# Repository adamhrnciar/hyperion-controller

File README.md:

# Hyperion: antweight combat robot controller

Open-source all-in-one controller for 150 g antweight combat robots. It combines an RC receiver
input, two brushed drive motor drivers, power handling and an IMU on a 34 × 28 mm 2-layer board.

Designed by Team Hyperion (Faculty of Electrical Engineering and Communication, Brno University of
Technology) for the Czech Combat Robot League (Česká liga bojových robotů, FLS Battlebots).

| Top | Bottom |
|---|---|
|  |  |

## Status

**Revision v1.2: unbuilt prototype; ordering is on hold.** The recovered 2026-11-13 Konnect review
reported no DRC, connectivity or schematic-parity violations and one understood ERC warning on
the IMU's unused SDx pin. Assembly process, sourcing and the remaining checks in the
[pre-order review](docs/v1.2-preorder-review-2026-11-13.md) still need resolution. Prototype build
and physical bring-up have not happened.

## Features

- **MCU:** RP2354A (RP2350 with 2 MB internal flash), 12 MHz crystal
- **Drive:** 2× TI DRV8231A brushed H-bridge, 4.5–33 V, current limit about 1.5 A per channel
  (IPROPI current regulation). Current feedback goes to the ADC for telemetry.
- **Input power:** 2–4S LiPo
  - reverse-polarity protection (AON7403 P-FET)
  - SMF18A TVS
  - battery voltage sensing
- **Rails:**
  - 5 V buck (LMR51610) for the receiver and servo/ESC signal header
  - 3.3 V LDO (ME6211)
- **Receiver input:** universal UART/RC pads for ELRS/CRSF, SBUS, iBUS and PPM, with a 5 V supply
  for the receiver
- **Outputs:** 4 PWM pads (weapon ESC, servo, spare), each with a 5 V/GND pad
- **IMU:** LSM6DSV32X (±32 g) for auto-invert and heading hold
- **Programming:** USB pads (UF2 bootloader, BOOT pad) and SWD pads
- **Status LEDs:** red and green
- **Board:** 34 × 28 mm, 2 layers, 1.6 mm FR-4. Battery and motor pads sit on the board edge.

## Motor target

- **Drive target:** 1–2 N10/N20 gearmotors per side on a 2–4S supply, with about 1.5 A regulated
  per channel (1.47 A nominal, set by R_IPROPI = 1.5 kΩ with VREF on 3.3 V). Motors sharing a
  channel share that limit. Choose motors rated for the applied voltage; this is not a claim
  that every N10/N20 is suitable for direct 4S operation.
- **Thermal limit:** 1.47 A is a current-regulation setting, not a measured continuous rating.
  Sustained pushing and stall tests on 2S, 3S and 4S remain open. Do not increase the limit to
  compensate for a motor that stalls above it.
- **Compared with the Malenki Nano HV** (1 A continuous / 3 A peak on 3 channels, AFHDS 2A
  receiver only, no BEC): Hyperion targets the same small-motor class and adds a 5 V BEC, an IMU,
  current/battery sensing and external receiver inputs. Its continuous rating still needs
  measurement, and its nominal regulated limit is 1.47 A rather than a specified 3 A burst.
  Firmware currently supports SBUS, CRSF and two-channel PWM; transmitter telemetry, iBUS and
  PPM are planned.
- **Not for beetleweight drive.** Beetleweight drive motors need 5–12 A per channel. Hyperion can
  still be the brain of such a robot, driving external ESCs from its PWM pads.

## Repository layout

```
hardware/   KiCad 10 project (schematic, PCB, project symbol and footprint libraries)
fab/        Manufacturing files for v1.2: Gerbers + drill (zip), BOM, pick-and-place, DRC report
docs/       Schematic PDF
firmware/   Firmware (Raspberry Pi Pico SDK, C) and the bring-up plan
images/     Renders and logo
```

## Building

- **PCB:** upload `fab/hyperion-v1.2-gerbers.zip`. 2 layers, 1.6 mm. Smallest features: 0.2 mm
  track/space and 0.3 mm drill. The RP2354A's 0.4 mm-pitch QFN needs a stencil.
- **Assembly:** `fab/hyperion-v1.2-bom.csv` lists LCSC and manufacturer part numbers.
  `fab/hyperion-v1.2-pos.csv` has the pick-and-place data. C3, the 100 µF bulk capacitor, is not
  placed; it is hand-wired to its pads. The TPx test pads are bare pads with no part.
- **PCBWay:** `fab/pcbway/` holds the candidate package: Gerbers, a BOM and centroid file with only
  the assembled parts, and `ASSEMBLY_NOTES.md` (board specs, DNP list, polarity notes, sourcing).
  Resolve the [pre-order review](docs/v1.2-preorder-review-2026-11-13.md) before releasing it.
- **Opening the design:** requires KiCad 10. The custom symbols and footprints are in
  `hardware/hyperion.kicad_sym` and `hardware/hyperion.pretty`.
- **Source of truth:** develop in [hyperion-controller](https://github.com/adamhrnciar/hyperion-controller).
  The `hyperion-controller/` subtree in `antweight-analysis` is a mirror. Its older
  `antweight/pcb/hyperion/` directory is historical; do not generate new manufacturing files from it.

## Firmware

`firmware/` holds the first firmware, written in C with the Raspberry Pi Pico SDK. It builds, but
has not run on a board yet. [firmware/README.md](firmware/README.md) covers building, settings,
stick and motor conventions, and the safety behaviour. [firmware/BRINGUP.md](firmware/BRINGUP.md)
is the test plan for the first boards.

Done:
- SBUS, CRSF and PWM receiver input with failsafe. On signal loss the drive motors brake and the
  weapon ESC gets no pulses.
- Arming interlock: the robot only arms with the drive stick centred and the weapon stick down.
  A dropout shorter than 1 s during a match resumes driving at once.
- tank mixing, DRV8231A drive, weapon ESC output on PWM1
- IMU, battery voltage and motor current readout
- bring-up test modes, including a stall test for the drivers' thermal shutdown

Planned:
- iBUS and PPM input
- IMU auto-invert and heading hold
- current and battery telemetry to the transmitter

## Buying a board

Assembled and tested boards will be sold once v1.2 has passed testing. Buying one supports
further development. You are also free to build your own from the files here.

## License

The hardware is licensed under [CERN-OHL-S-2.0](LICENSE). You may make, modify and sell the board,
as long as you publish the source of any modified version under the same licence.

The firmware in `firmware/` is licensed under [GPL-3.0-or-later](firmware/LICENSE). You may use,
modify and sell it, as long as you publish the source of any modified version you distribute under
the same licence. `firmware/pico_sdk_import.cmake` is BSD-3-Clause (Raspberry Pi Ltd).

The licence does not cover the name "Hyperion" or the Hyperion logo. Modified or third-party boards
must not be sold under that name or with that logo.

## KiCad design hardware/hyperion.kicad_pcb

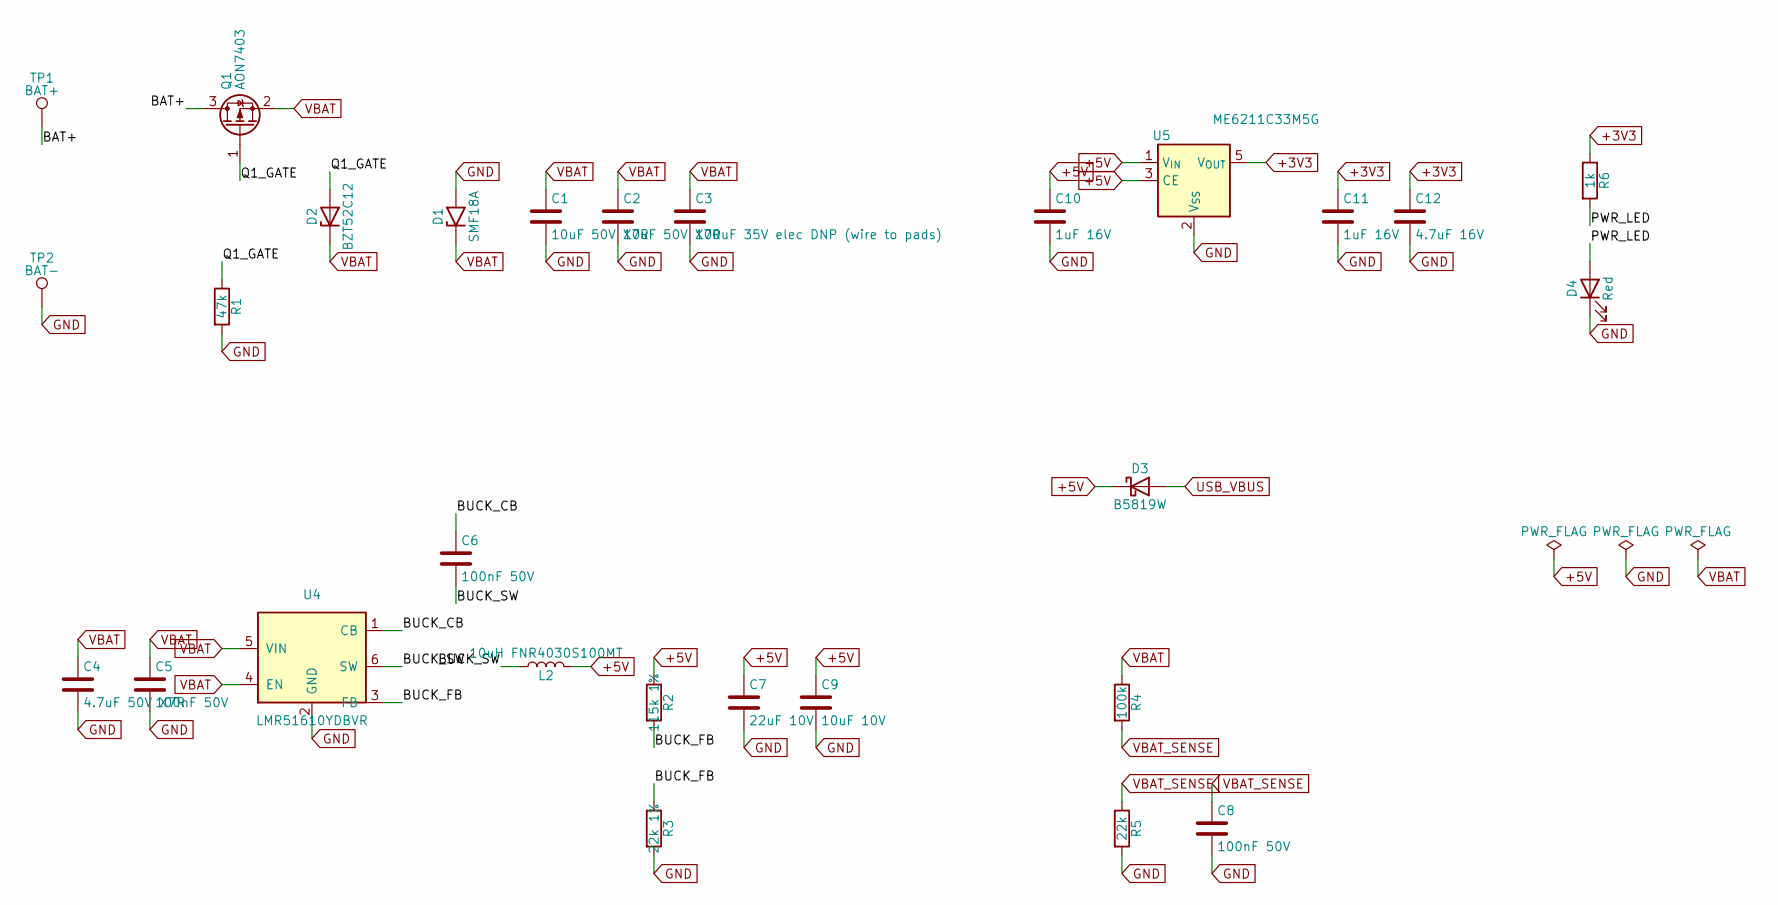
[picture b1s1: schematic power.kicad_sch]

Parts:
C1, C2: 10uF 50V X7R; C_1206_3216Metric; MPN CL31B106KBHNNNE; LCSC C89632
C3: 100uF 35V elec DNP (wire to pads); C_1206_3216Metric; MPN RVE100UF35V67RV0072 (optional, hand-wir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; LCSC C2836437
C4: 4.7uF 50V X7R; C_1206_3216Metric; MPN HGC1206R7475K500NSPJ; LCSC C7472974
C5, C6, C8: 100nF 50V; C_0603_1608Metric; MPN 0603B104M500NT; LCSC C286510
C7: 22uF 10V; C_0805_2012Metric; MPN CL21A226MPQNNNE; LCSC C29277
C9: 10uF 10V; C_0603_1608Metric; MPN CL10A106KP8NNNC; LCSC C19702
C10, C11: 1uF 16V; C_0603_1608Metric; MPN TCC0603X5R105K160CT; LCSC C696901
C12: 4.7uF 16V; C_0603_1608Metric; MPN CL10A475KO8NNNC; LCSC C19666
D1: SMF18A; D_SOD-123F; MPN SMF18A (JSCJ); LCSC C1509591
D2: BZT52C12; D_SOD-123; MPN BZT52C12 (MDD); LCSC C173429
D3: B5819W; D_SOD-123; MPN B5819W (MDD); LCSC C64885
D4: Red; LED_0603_1608Metric; MPN KT-0603R; LCSC C2286
L2: 10uH FNR4030S100MT; L_Changjiang_FNR4030S; MPN FNR4030S100MT; LCSC C167879
Q1: AON7403; AON7403_PowerPAK1212-8_GSD; MPN AON7403 (TECH PUBLIC); LCSC C5310961
R1: 47k; R_0603_1608Metric; MPN 0603WAF4702T5E; LCSC C25819
R2: 115k 1%; R_0603_1608Metric; MPN 0603WAF1153T5E; LCSC C22783
R3: 22k 1%; R_0603_1608Metric; MPN 0603WAF2202T5E; LCSC C31850
R4: 100k; R_0603_1608Metric; MPN 0603WAF1003T5E; LCSC C25803
R5: 22k; R_0603_1608Metric; MPN 0603WAF2202T5E; LCSC C31850
R6: 1k; R_0603_1608Metric; MPN 0603WAF1001T5E; LCSC C21190
TP1: BAT+; TestPoint_Pad_2.5x2.5mm
TP2: BAT-; TestPoint_Pad_2.5x2.5mm
U4: LMR51610YDBVR; SOT-23-6; MPN LMR51610YDBVR; LCSC C22427220
U5: ME6211C33M5G; SOT-23-5; MPN ME6211C33M5G-N; LCSC C82942

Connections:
+3V3: C11.1, C12.1, R6.1, U5.5 (V_{OUT}); also elsewhere on the board
+5V: C7.1, C9.1, C10.1, D3.1 (K), L2.2, R2.1, U5.1 (V_{IN}), U5.3 (CE); also elsewhere on the board
/Power/BAT+: Q1.3 (D), TP1.1 (1_1)
/Power/BUCK_CB: C6.1, U4.1 (CB)
/Power/BUCK_FB: R2.2, R3.1, U4.3 (FB)
/Power/BUCK_SW: C6.2, L2.1, U4.6 (SW)
/Power/PWR_LED: D4.2 (A), R6.2
/Power/Q1_GATE: D2.2 (A), Q1.1 (G), R1.1
GND: C1.2, C2.2, C3.2, C4.2, C5.2, C7.2, C8.2, C9.2, C10.2, C11.2, C12.2, D1.2 (A2), D4.1 (K), R1.2, R3.2, R5.2, TP2.1 (1_1), U4.2 (GND), U5.2 (V_{SS}); also elsewhere on the board
USB_VBUS: D3.2 (A); also elsewhere on the board
VBAT: C1.1, C2.1, C3.1, C4.1, C5.1, D1.1 (A1), D2.1 (K), Q1.2 (S), R4.1, U4.4 (EN), U4.5 (VIN); also elsewhere on the board
VBAT_SENSE: C8.1, R4.2, R5.1; also elsewhere on the board

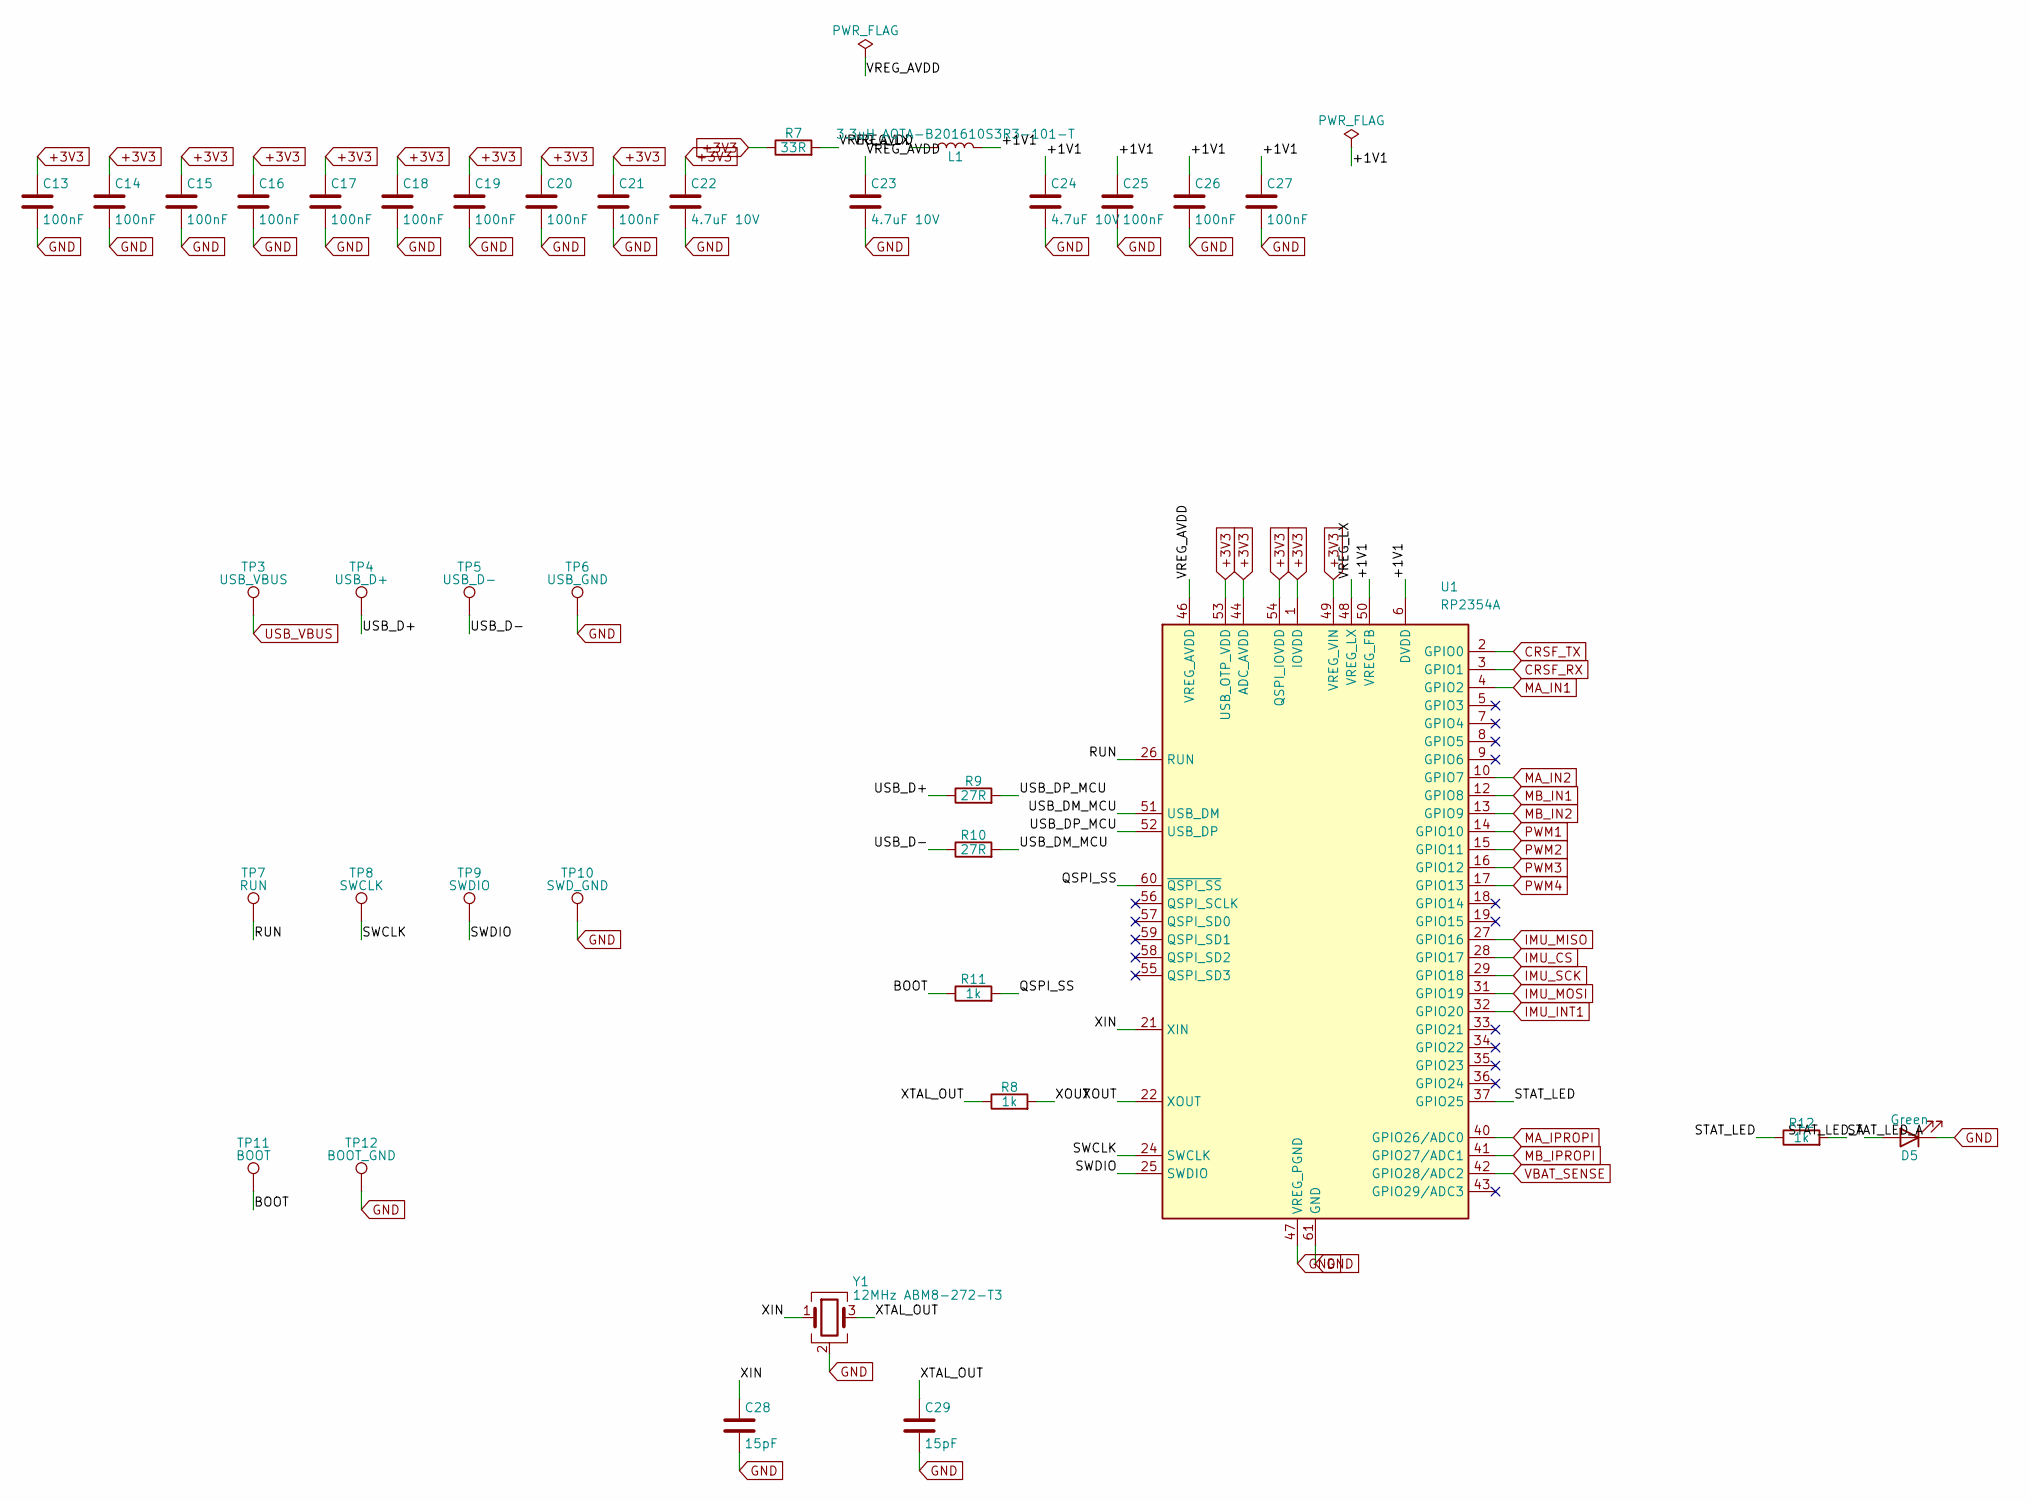
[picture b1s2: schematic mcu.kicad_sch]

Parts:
C13, C14, C15, C16, C17, C18, C19, C20, C21, C25, C26, C27: 100nF; C_0402_1005Metric; MPN CL05B104KO5NNNC; LCSC C1525
C22, C23, C24: 4.7uF 10V; C_0402_1005Metric; MPN CL05A475MP5NRNC; LCSC C23733
C28, C29: 15pF; C_0402_1005Metric; MPN 0402CG150J500NT; LCSC C1548
D5: Green; LED_0603_1608Metric; MPN P2-0603G1TS2-06T-002; LCSC C7496818
L1: 3.3uH AOTA-B201610S3R3-101-T; L_Murata_DFE201610P; MPN AOTA-B201610S3R3-101-T; LCSC C42411119
R7: 33R; R_0402_1005Metric; MPN 0402WGF330JTCE; LCSC C25105
R8, R11, R12: 1k; R_0402_1005Metric; MPN 0402WGF1001TCE; LCSC C11702
R9, R10: 27R; R_0402_1005Metric; MPN RC-02K27R0FT; LCSC C140174
TP3: USB_VBUS; TestPoint_Pad_1.0x1.0mm
TP4: USB_D+; TestPoint_Pad_1.0x1.0mm
TP5: USB_D-; TestPoint_Pad_1.0x1.0mm
TP6: USB_GND; TestPoint_Pad_1.0x1.0mm
TP7: RUN; TestPoint_Pad_1.0x1.0mm
TP8: SWCLK; TestPoint_Pad_1.0x1.0mm
TP9: SWDIO; TestPoint_Pad_1.0x1.0mm
TP10: SWD_GND; TestPoint_Pad_1.0x1.0mm
TP11: BOOT; TestPoint_Pad_1.0x1.0mm
TP12: BOOT_GND; TestPoint_Pad_1.0x1.0mm
U1: RP2354A; RP2354A_QFN-60_CircuitNinja; MPN RP2354A; LCSC C41378174
Y1: 12MHz ABM8-272-T3; Crystal_SMD_3225-4Pin_3.2x2.5mm; MPN ABM8-272-T3; LCSC C20625731

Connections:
+3V3: C13.1, C14.1, C15.1, C16.1, C17.1, C18.1, C19.1, C20.1, C21.1, C22.1, R7.1, U1.1 (IOVDD), U1.11 (IOVDD), U1.20 (IOVDD), U1.30 (IOVDD), U1.38 (IOVDD), U1.44 (ADC_AVDD), U1.45 (IOVDD), U1.49 (VREG_VIN), U1.53 (USB_OTP_VDD), U1.54 (QSPI_IOVDD); also elsewhere on the board
/MCU/+1V1: C24.1, C25.1, C26.1, C27.1, L1.2, U1.6 (DVDD), U1.23 (DVDD), U1.39 (DVDD), U1.50 (VREG_FB)
/MCU/BOOT: R11.1, TP11.1 (1_1)
/MCU/QSPI_SS: R11.2, U1.60 (~QSPI_SS)
/MCU/RUN: TP7.1 (1_1), U1.26 (RUN)
/MCU/STAT_LED: R12.1, U1.37 (GPIO25)
/MCU/STAT_LED_A: D5.2 (A), R12.2
/MCU/SWCLK: TP8.1 (1_1), U1.24 (SWCLK)
/MCU/SWDIO: TP9.1 (1_1), U1.25 (SWDIO)
/MCU/USB_D+: R9.1, TP4.1 (1_1)
/MCU/USB_D-: R10.1, TP5.1 (1_1)
/MCU/USB_DM_MCU: R10.2, U1.51 (USB_DM)
/MCU/USB_DP_MCU: R9.2, U1.52 (USB_DP)
/MCU/VREG_AVDD: C23.1, R7.2, U1.46 (VREG_AVDD)
/MCU/VREG_LX: L1.1, U1.48 (VREG_LX)
/MCU/XIN: C28.1, U1.21 (XIN), Y1.1
/MCU/XOUT: R8.2, U1.22 (XOUT)
/MCU/XTAL_OUT: C29.1, R8.1, Y1.3
CRSF_RX: U1.3 (GPIO1); also elsewhere on the board
CRSF_TX: U1.2 (GPIO0); also elsewhere on the board
GND: C13.2, C14.2, C15.2, C16.2, C17.2, C18.2, C19.2, C20.2, C21.2, C22.2, C23.2, C24.2, C25.2, C26.2, C27.2, C28.2, C29.2, D5.1 (K), TP6.1 (1_1), TP10.1 (1_1), TP12.1 (1_1), U1.47 (VREG_PGND), U1.61 (GND), Y1.2 (G), Y1.4 (G); also elsewhere on the board
IMU_CS: U1.28 (GPIO17); also elsewhere on the board
IMU_INT1: U1.32 (GPIO20); also elsewhere on the board
IMU_MISO: U1.27 (GPIO16); also elsewhere on the board
IMU_MOSI: U1.31 (GPIO19); also elsewhere on the board
IMU_SCK: U1.29 (GPIO18); also elsewhere on the board
MA_IN1: U1.4 (GPIO2); also elsewhere on the board
MA_IN2: U1.10 (GPIO7); also elsewhere on the board
MA_IPROPI: U1.40 (GPIO26/ADC0); also elsewhere on the board
MB_IN1: U1.12 (GPIO8); also elsewhere on the board
MB_IN2: U1.13 (GPIO9); also elsewhere on the board
MB_IPROPI: U1.41 (GPIO27/ADC1); also elsewhere on the board
PWM1: U1.14 (GPIO10); also elsewhere on the board
PWM2: U1.15 (GPIO11); also elsewhere on the board
PWM3: U1.16 (GPIO12); also elsewhere on the board
PWM4: U1.17 (GPIO13); also elsewhere on the board
USB_VBUS: TP3.1 (1_1); also elsewhere on the board
VBAT_SENSE: U1.42 (GPIO28/ADC2); also elsewhere on the board

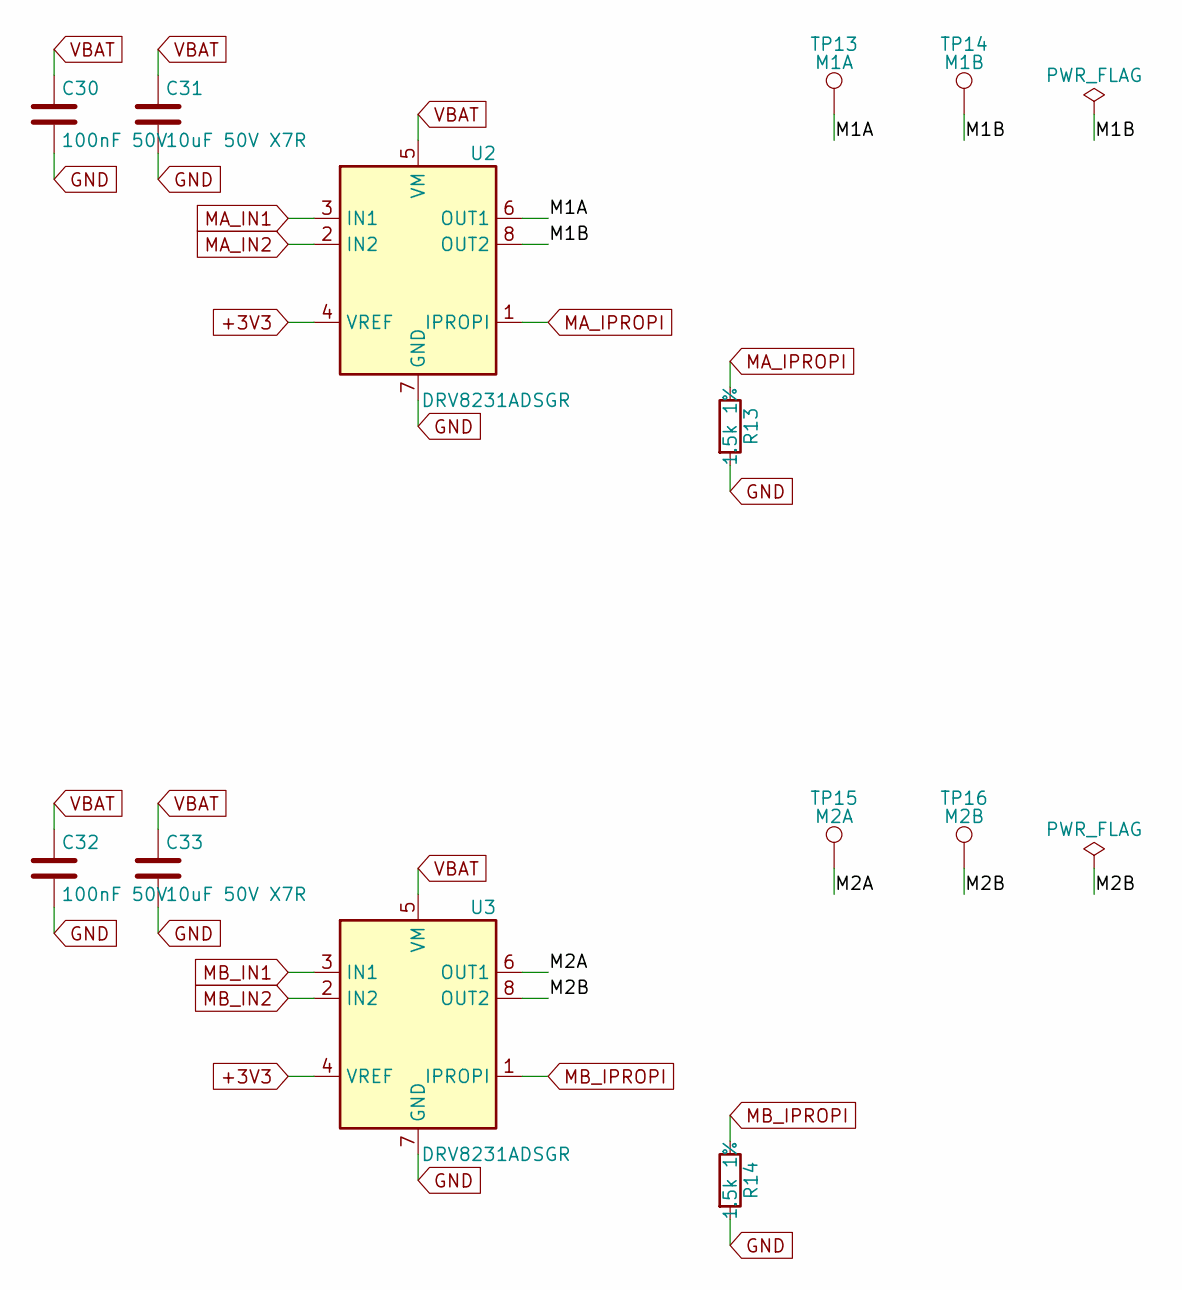
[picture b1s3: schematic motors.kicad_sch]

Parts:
C30, C32: 100nF 50V; C_0603_1608Metric; MPN 0603B104M500NT; LCSC C286510
C31, C33: 10uF 50V X7R; C_1206_3216Metric; MPN CL31B106KBHNNNE; LCSC C89632
R13, R14: 1.5k 1%; R_0603_1608Metric; MPN 0603WAF1501T5E; LCSC C22843
TP13: M1A; TestPoint_Pad_2.0x2.0mm
TP14: M1B; TestPoint_Pad_2.0x2.0mm
TP15: M2A; TestPoint_Pad_2.0x2.0mm
TP16: M2B; TestPoint_Pad_2.0x2.0mm
U2, U3: DRV8231ADSGR; Texas_DSG0008A_WSON-8-1EP_2x2mm_P0.5mm_EP0.9x1.6mm; MPN DRV8231ADSGR; LCSC C5139865

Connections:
+3V3: U2.4 (VREF), U3.4 (VREF); also elsewhere on the board
/Motors/M1A: TP13.1 (1_1), U2.6 (OUT1)
/Motors/M1B: TP14.1 (1_1), U2.8 (OUT2)
/Motors/M2A: TP15.1 (1_1), U3.6 (OUT1)
/Motors/M2B: TP16.1 (1_1), U3.8 (OUT2)
GND: C30.2, C31.2, C32.2, C33.2, R13.2, R14.2, U2.7 (GND), U2.9 (GND), U3.7 (GND), U3.9 (GND); also elsewhere on the board
MA_IN1: U2.3 (IN1); also elsewhere on the board
MA_IN2: U2.2 (IN2); also elsewhere on the board
MA_IPROPI: R13.1, U2.1 (IPROPI); also elsewhere on the board
MB_IN1: U3.3 (IN1); also elsewhere on the board
MB_IN2: U3.2 (IN2); also elsewhere on the board
MB_IPROPI: R14.1, U3.1 (IPROPI); also elsewhere on the board
VBAT: C30.1, C31.1, C32.1, C33.1, U2.5 (VM), U3.5 (VM); also elsewhere on the board

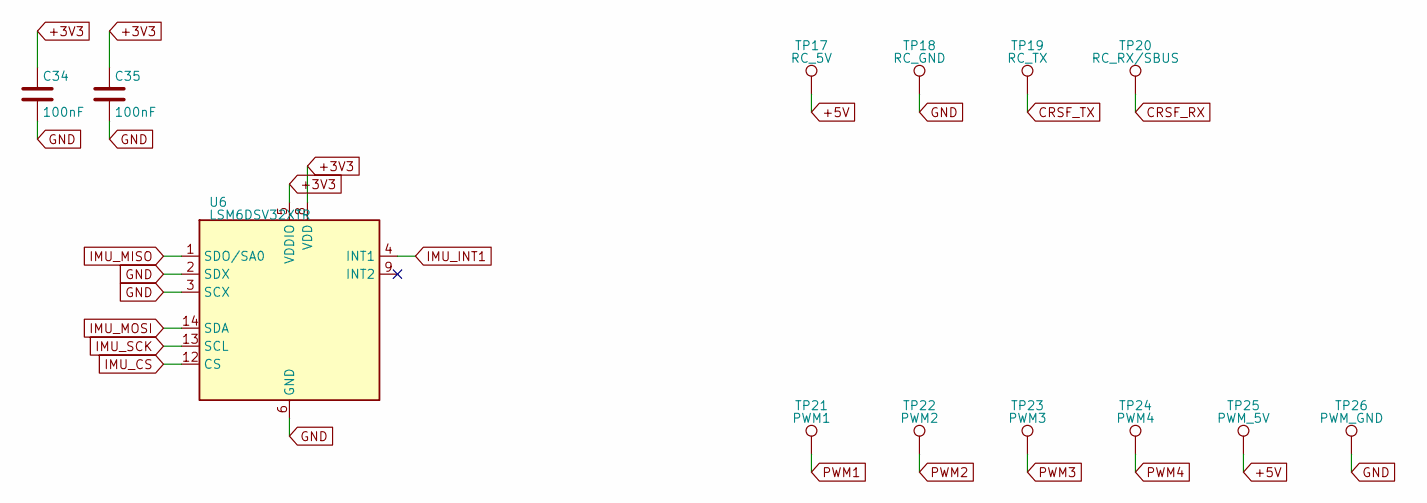
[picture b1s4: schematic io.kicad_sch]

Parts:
C34, C35: 100nF; C_0402_1005Metric; MPN CL05B104KO5NNNC; LCSC C1525
TP17: RC_5V; TestPoint_Pad_1.0x1.0mm
TP18: RC_GND; TestPoint_Pad_1.0x1.0mm
TP19: RC_TX; TestPoint_Pad_1.0x1.0mm
TP20: RC_RX/SBUS; TestPoint_Pad_1.0x1.0mm
TP21: PWM1; TestPoint_Pad_1.0x1.0mm
TP22: PWM2; TestPoint_Pad_1.0x1.0mm
TP23: PWM3; TestPoint_Pad_1.0x1.0mm
TP24: PWM4; TestPoint_Pad_1.0x1.0mm
TP25: PWM_5V; TestPoint_Pad_1.0x1.0mm
TP26: PWM_GND; TestPoint_Pad_1.0x1.0mm
U6: LSM6DSV32XTR; LGA-14_3x2.5mm_P0.5mm_CircuitNinja; MPN LSM6DSV32XTR; LCSC C22461202

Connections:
+3V3: C34.1, C35.1, U6.5 (VDDIO), U6.8 (VDD); also elsewhere on the board
+5V: TP17.1 (1_1), TP25.1 (1_1); also elsewhere on the board
CRSF_RX: TP20.1 (1_1); also elsewhere on the board
CRSF_TX: TP19.1 (1_1); also elsewhere on the board
GND: C34.2, C35.2, TP18.1 (1_1), TP26.1 (1_1), U6.2 (SDX), U6.3 (SCX), U6.6 (GND), U6.7 (GND); also elsewhere on the board
IMU_CS: U6.12 (CS); also elsewhere on the board
IMU_INT1: U6.4 (INT1); also elsewhere on the board
IMU_MISO: U6.1 (SDO/SA0); also elsewhere on the board
IMU_MOSI: U6.14 (SDA); also elsewhere on the board
IMU_SCK: U6.13 (SCL); also elsewhere on the board
PWM1: TP21.1 (1_1); also elsewhere on the board
PWM2: TP22.1 (1_1); also elsewhere on the board
PWM3: TP23.1 (1_1); also elsewhere on the board
PWM4: TP24.1 (1_1); also elsewhere on the board

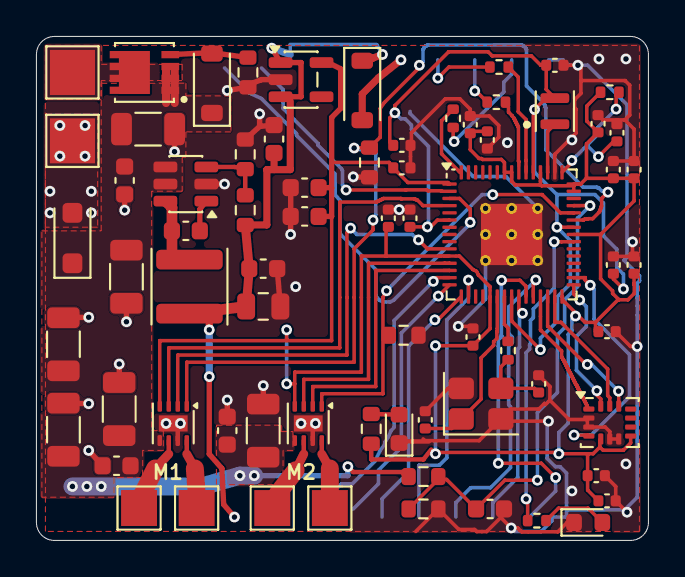
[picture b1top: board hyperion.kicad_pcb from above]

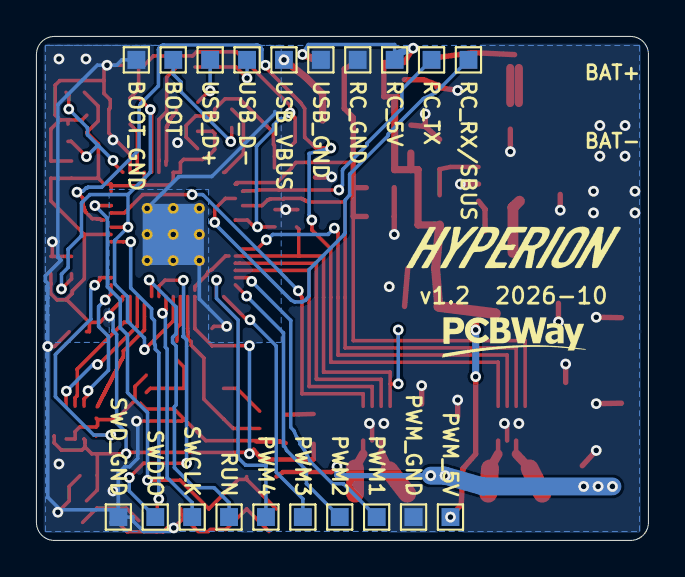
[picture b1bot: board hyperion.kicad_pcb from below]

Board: 2 copper layers, 34.0 x 28.0 mm, 90 parts (20 on the bottom side), 50 nets.

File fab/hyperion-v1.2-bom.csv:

"Reference","Value","Footprint","QUANTITY","DNP","LCSC","MPN"
"C1,C2,C31,C33","10uF 50V X7R","Capacitor_SMD:C_1206_3216Metric","4","","C89632","CL31B106KBHNNNE"
"C3","100uF 35V elec DNP (wire to pads)","Capacitor_SMD:C_1206_3216Metric","1","","C2836437","RVE100UF35V67RV0072 (optional, hand-wired)"
"C4","4.7uF 50V X7R","Capacitor_SMD:C_1206_3216Metric","1","","C7472974","HGC1206R7475K500NSPJ"
"C5,C6,C8,C30,C32","100nF 50V","Capacitor_SMD:C_0603_1608Metric","5","","C286510","0603B104M500NT"
"C7","22uF 10V","Capacitor_SMD:C_0805_2012Metric","1","","C29277","CL21A226MPQNNNE"
"C9","10uF 10V","Capacitor_SMD:C_0603_1608Metric","1","","C19702","CL10A106KP8NNNC"
"C10,C11","1uF 16V","Capacitor_SMD:C_0603_1608Metric","2","","C696901","TCC0603X5R105K160CT"
"C12","4.7uF 16V","Capacitor_SMD:C_0603_1608Metric","1","","C19666","CL10A475KO8NNNC"
"C13-C21,C25-C27,C34,C35","100nF","Capacitor_SMD:C_0402_1005Metric","14","","C1525","CL05B104KO5NNNC"
"C22-C24","4.7uF 10V","Capacitor_SMD:C_0402_1005Metric","3","","C23733","CL05A475MP5NRNC"
"C28,C29","15pF","Capacitor_SMD:C_0402_1005Metric","2","","C1548","0402CG150J500NT"
"D1","SMF18A","Diode_SMD:D_SOD-123F","1","","C1509591","SMF18A (JSCJ)"
"D2","BZT52C12","Diode_SMD:D_SOD-123","1","","C173429","BZT52C12 (MDD)"
"D3","B5819W","Diode_SMD:D_SOD-123","1","","C64885","B5819W (MDD)"
"D4","Red","LED_SMD:LED_0603_1608Metric","1","","C2286","KT-0603R"
"D5","Green","LED_SMD:LED_0603_1608Metric","1","","C7496818","P2-0603G1TS2-06T-002"
"L1","3.3uH AOTA-B201610S3R3-101-T","Inductor_SMD:L_Murata_DFE201610P","1","","C42411119","AOTA-B201610S3R3-101-T"
"L2","10uH FNR4030S100MT","Inductor_SMD:L_Changjiang_FNR4030S","1","","C167879","FNR4030S100MT"
"Q1","AON7403","hyperion:AON7403_PowerPAK1212-8_GSD","1","","C5310961","AON7403 (TECH PUBLIC)"
"R1","47k","Resistor_SMD:R_0603_1608Metric","1","","C25819","0603WAF4702T5E"
"R2","115k 1%","Resistor_SMD:R_0603_1608Metric","1","","C22783","0603WAF1153T5E"
"R3","22k 1%","Resistor_SMD:R_0603_1608Metric","1","","C31850","0603WAF2202T5E"
"R4","100k","Resistor_SMD:R_0603_1608Metric","1","","C25803","0603WAF1003T5E"
"R5","22k","Resistor_SMD:R_0603_1608Metric","1","","C31850","0603WAF2202T5E"
"R6","1k","Resistor_SMD:R_0603_1608Metric","1","","C21190","0603WAF1001T5E"
"R7","33R","Resistor_SMD:R_0402_1005Metric","1","","C25105","0402WGF330JTCE"
"R8,R11,R12","1k","Resistor_SMD:R_0402_1005Metric","3","","C11702","0402WGF1001TCE"
"R9,R10","27R","Resistor_SMD:R_0402_1005Metric","2","","C140174","RC-02K27R0FT"
"R13,R14","1.5k 1%","Resistor_SMD:R_0603_1608Metric","2","","C22843","0603WAF1501T5E"
"TP1","BAT+","TestPoint:TestPoint_Pad_2.5x2.5mm","1","","",""
"TP2","BAT-","TestPoint:TestPoint_Pad_2.5x2.5mm","1","","",""
"TP3","USB_VBUS","TestPoint:TestPoint_Pad_1.0x1.0mm","1","","",""
"TP4","USB_D+","TestPoint:TestPoint_Pad_1.0x1.0mm","1","","",""
"TP5","USB_D-","TestPoint:TestPoint_Pad_1.0x1.0mm","1","","",""
"TP6","USB_GND","TestPoint:TestPoint_Pad_1.0x1.0mm","1","","",""
"TP7","RUN","TestPoint:TestPoint_Pad_1.0x1.0mm","1","","",""
"TP8","SWCLK","TestPoint:TestPoint_Pad_1.0x1.0mm","1","","",""
"TP9","SWDIO","TestPoint:TestPoint_Pad_1.0x1.0mm","1","","",""
"TP10","SWD_GND","TestPoint:TestPoint_Pad_1.0x1.0mm","1","","",""
"TP11","BOOT","TestPoint:TestPoint_Pad_1.0x1.0mm","1","","",""
"TP12","BOOT_GND","TestPoint:TestPoint_Pad_1.0x1.0mm","1","","",""
"TP13","M1A","TestPoint:TestPoint_Pad_2.0x2.0mm","1","","",""
"TP14","M1B","TestPoint:TestPoint_Pad_2.0x2.0mm","1","","",""
"TP15","M2A","TestPoint:TestPoint_Pad_2.0x2.0mm","1","","",""
"TP16","M2B","TestPoint:TestPoint_Pad_2.0x2.0mm","1","","",""
"TP17","RC_5V","TestPoint:TestPoint_Pad_1.0x1.0mm","1","","",""
"TP18","RC_GND","TestPoint:TestPoint_Pad_1.0x1.0mm","1","","",""
"TP19","RC_TX","TestPoint:TestPoint_Pad_1.0x1.0mm","1","","",""
"TP20","RC_RX/SBUS","TestPoint:TestPoint_Pad_1.0x1.0mm","1","","",""
"TP21","PWM1","TestPoint:TestPoint_Pad_1.0x1.0mm","1","","",""
"TP22","PWM2","TestPoint:TestPoint_Pad_1.0x1.0mm","1","","",""
"TP23","PWM3","TestPoint:TestPoint_Pad_1.0x1.0mm","1","","",""
"TP24","PWM4","TestPoint:TestPoint_Pad_1.0x1.0mm","1","","",""
"TP25","PWM_5V","TestPoint:TestPoint_Pad_1.0x1.0mm","1","","",""
"TP26","PWM_GND","TestPoint:TestPoint_Pad_1.0x1.0mm","1","","",""
"U1","RP2354A","hyperion:RP2354A_QFN-60_CircuitNinja","1","","C41378174","RP2354A"
"U2,U3","DRV8231ADSGR","Package_SON:Texas_DSG0008A_WSON-8-1EP_2x2mm_P0.5mm_EP0.9x1.6mm","2","","C5139865","DRV8231ADSGR"
"U4","LMR51610YDBVR","Package_TO_SOT_SMD:SOT-23-6","1","","C22427220","LMR51610YDBVR"
"U5","ME6211C33M5G","Package_TO_SOT_SMD:SOT-23-5","1","","C82942","ME6211C33M5G-N"
"U6","LSM6DSV32XTR","hyperion:LGA-14_3x2.5mm_P0.5mm_CircuitNinja","1","","C22461202","LSM6DSV32XTR"
"Y1","12MHz ABM8-272-T3","Crystal:Crystal_SMD_3225-4Pin_3.2x2.5mm","1","","C20625731","ABM8-272-T3"

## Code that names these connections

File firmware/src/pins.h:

// SPDX-License-Identifier: GPL-3.0-or-later
// Hyperion v1.2 pin map.
//
// Extracted from the KiCad netlist (hardware/hyperion.kicad_sch, exported with
// `kicad-cli sch export netlist`). Net names match the schematic; U1 pad
// numbers are for the RP2354A QFN-60.

#pragma once

// --- Receiver port (TP19 RC_TX, TP20 RC_RX/SBUS) ------------------------------
// UART0 pins. CRSF uses the hardware UART; SBUS uses PIO with the pad input
// inverted (GPIO INOVER); PWM/PPM input uses edge capture on the same pads.
#define PIN_RC_TX           0   // net CRSF_TX,   U1 pad 2,  TP19
#define PIN_RC_RX           1   // net CRSF_RX,   U1 pad 3,  TP20 (SBUS input)

// --- Motor A: U2 DRV8231A, outputs M1A/M1B (TP13/TP14) -----------------------
#define PIN_MA_IN1          2   // net MA_IN1, U1 pad 4,  PWM slice 1 A
#define PIN_MA_IN2          7   // net MA_IN2, U1 pad 10, PWM slice 3 B
#define PIN_MA_IPROPI       26  // net MA_IPROPI, U1 pad 40, ADC0, R13 1.5k

// --- Motor B: U3 DRV8231A, outputs M2A/M2B (TP15/TP16) -----------------------
#define PIN_MB_IN1          8   // net MB_IN1, U1 pad 12, PWM slice 4 A
#define PIN_MB_IN2          9   // net MB_IN2, U1 pad 13, PWM slice 4 B
#define PIN_MB_IPROPI       27  // net MB_IPROPI, U1 pad 41, ADC1, R14 1.5k

// --- PWM output pads TP21..TP24 (weapon ESC, servo, spare) ------------------
#define PIN_PWM1            10  // net PWM1, U1 pad 14, PWM slice 5 A
#define PIN_PWM2            11  // net PWM2, U1 pad 15, PWM slice 5 B
#define PIN_PWM3            12  // net PWM3, U1 pad 16, PWM slice 6 A
#define PIN_PWM4            13  // net PWM4, U1 pad 17, PWM slice 6 B

// --- IMU: U6 LSM6DSV32X on SPI0 ----------------------------------------------
#define IMU_SPI             spi0
#define PIN_IMU_MISO        16  // net IMU_MISO, U1 pad 27, U6 pin 1 SDO/SA0
#define PIN_IMU_CS          17  // net IMU_CS,   U1 pad 28, U6 pin 12 CS
#define PIN_IMU_SCK         18  // net IMU_SCK,  U1 pad 29, U6 pin 13 SCL/SPC
#define PIN_IMU_MOSI        19  // net IMU_MOSI, U1 pad 31, U6 pin 14 SDA/SDI
#define PIN_IMU_INT1        20  // net IMU_INT1, U1 pad 32, U6 pin 4
// U6 INT2 (pin 9) is not connected. SDx/SCx (OIS aux SPI) are tied to GND.

// --- Status LED ---------------------------------------------------------------
// Green D5 via R12 1k. The red LED D4 is a power LED on +3V3 via R6, not an MCU pin.
#define PIN_LED_STATUS      25  // net STAT_LED, U1 pad 37

// --- Analog -------------------------------------------------------------------
#define PIN_VBAT_SENSE      28  // net VBAT_SENSE, U1 pad 42, ADC2
#define ADC_CH_MA_IPROPI    0
#define ADC_CH_MB_IPROPI    1
#define ADC_CH_VBAT         2

// VBAT divider R4 100k (top) / R5 22k (bottom), C8 100 nF.
#define VBAT_DIV_TOP_OHM    100000u
#define VBAT_DIV_BOT_OHM    22000u

// DRV8231A current sense: I_IPROPI = I_LS * 1500 uA/A into R_IPROPI = 1.5 kOhm,
// so V_IPROPI = 2.25 V per A. VREF is tied to +3V3, so I_TRIP = 3.3 / 2.25 = 1.47 A.
#define DRV_AIPROPI_UA_PER_A 1500u
#define DRV_RIPROPI_OHM      1500u

// --- Unused -------------------------------------------------------------------
// GPIO3, 4, 5, 6, 14, 15, 21, 22, 23, 24, 29 (ADC3) are not connected.
// Debug: SWCLK TP8, SWDIO TP9, RUN TP7. BOOT TP11 (QSPI_SS via R11 1k).
// USB: D+ TP4, D- TP5 (27R series R9/R10), VBUS TP3 feeds +5V through D3.
